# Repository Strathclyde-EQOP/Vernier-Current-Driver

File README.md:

# Vernier Current Driver

The Vernier Current Driver is an ultra low noise, programmable, bi-polar current source. It comes in two flavours:

1. Low Current Driver (LCD): designed to output current up to ~50 mA
2. High Current Driver (HCD): designed to output currents from ~50 mA to ~250 mA

## Releases

Checkout the [latest release](https://github.com/Strathclyde-EQOP/Vernier-Current-Driver/releases/latest) to download the latest verified version of the design. Releases include PDF schematics and gerber files, so there is no need to install/understand KiCAD in order to make a board.

Checkout the [dev branch](https://github.com/Strathclyde-EQOP/Vernier-Current-Driver/tree/dev) for the most up to date (but probably untested!) design.

## Performance

Three sample devices have been tested. For full details, see the companion paper or take a look a look in the [Testing](/Doc/Testing/) folder.

The headlines results:

|Configuration|CH1|CH2|CH3|
|---|---|---|---|
|LCD@10 mA<sub>MAX</sub> (10 ± 5 Hz average noise) | 151.1 pA√Hz | 147.4 pA√Hz | 146.3 pA√Hz |
|LCD@2.5 mA<sub>MAX</sub> (10 ± 5 Hz average noise) | 37.6 pA√Hz | 38.2 pA√Hz | 37.7 pA√Hz |
|HCD@250 mA<sub>MAX</sub> (10 ± 5 Hz average noise) | 4114.2 pA√Hz | 4125.3 pA√Hz | 4124.1 pA√Hz |
|LCD@10 mA<sub>MAX</sub> (10 ± 5 Hz relative average noise) | 15.05 ppb√Hz | 14.68 ppb√Hz | 14.57 ppb√Hz |
|LCD@2.5 mA<sub>MAX</sub> (10 ± 5 Hz relative average noise) | 15.06 ppb√Hz | 15.29 ppb√Hz | 15.10 ppb√Hz |
|HCD@250 mA<sub>MAX</sub> (10 ± 5 Hz relative average noise) | 16.46 ppb√Hz | 16.50 ppb√Hz | 16.50 ppb√Hz |

## Manual

For more information checkout the [Getting Started Guide](Doc/README.md).

## Publication

If you're the academic type, lots more detail on the design and testing of the Vernier Current Source can be found in our open-access paper, available as a pre-print on [arXiv](https://arxiv.org/abs/2207.10348).

## Citing

When citing this work in an academic context, please cite the paper as you normally would.

Outside of academic work, please link directly to this GitHub repo.

Lastly, if you make one and you like it (or don't like it), we would love to know!

## License

This work is licensed under a [Creative Commons Attribution-ShareAlike 4.0 International License](https://creativecommons.org/licenses/by-sa/4.0/).

## Authors

This work was created by [Marcin Mrozowski](https://eqop.phys.strath.ac.uk/people/marcin-mrozowski/) and [Iain Chalmers](https://www.linkedin.com/in/iain-chalmers-0394753b)
from the [Experimental Quantum Optics and Photonics](http://photonics.phys.strath.ac.uk/)
group at the University of Strathclyde.

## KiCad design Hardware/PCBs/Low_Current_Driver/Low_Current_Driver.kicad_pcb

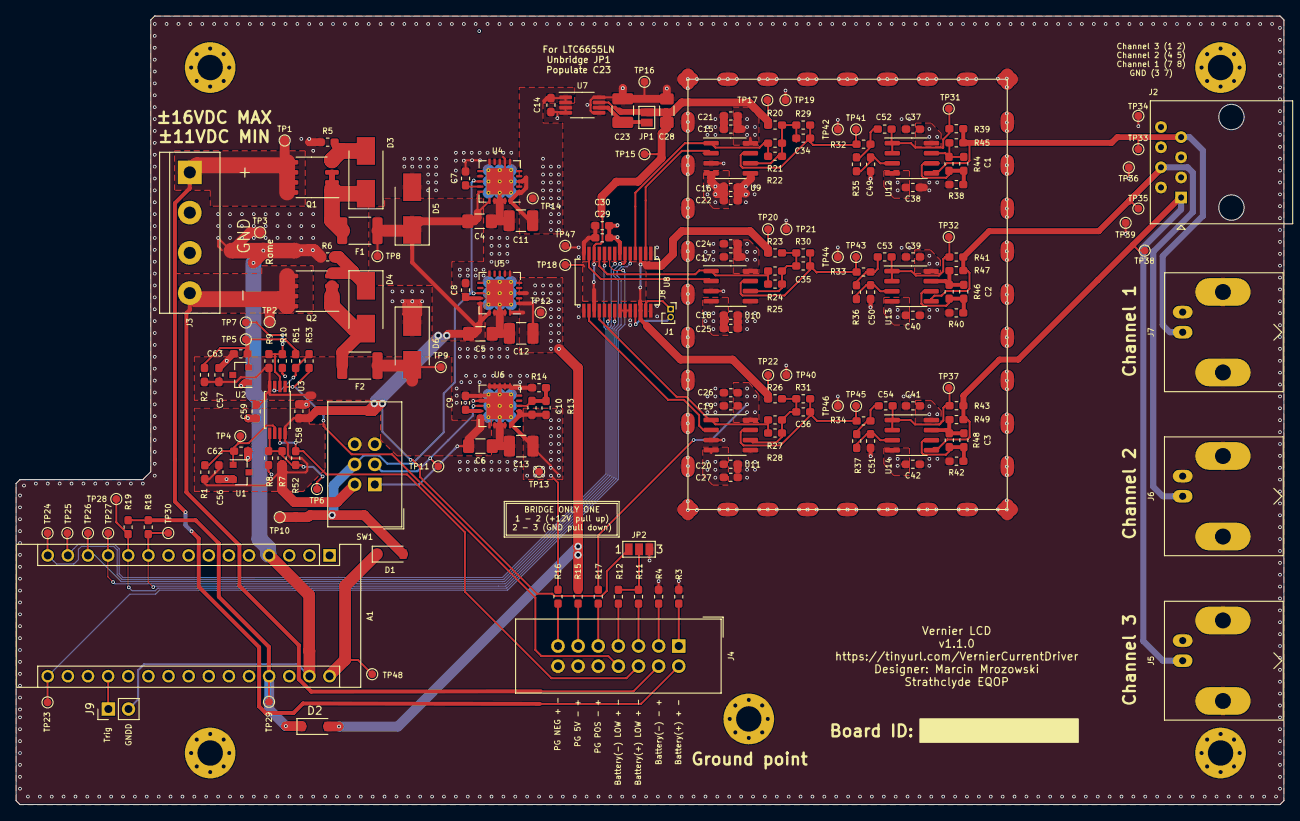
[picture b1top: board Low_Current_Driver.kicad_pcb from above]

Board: 4 copper layers, 160.0 x 99.5 mm, 194 parts (0 on the bottom side), 78 nets.

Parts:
A1: Arduino_Nano_Every; Arduino_Nano
C1, C2, C3, C7, C8, C9, C21, C22, C24, C25, C26, C27, C49, C50, C51, C52, C53, C54: 1u; C_0603_1608Metric_Pad1.05x0.95mm_HandSolder
C4, C5, C6, C28: 10u; C_1206_3216Metric_Pad1.42x1.75mm_HandSolder
C10, C29: 10n; C_0603_1608Metric_Pad1.05x0.95mm_HandSolder
C11, C12, C13, C23: 47u; C_1210_3225Metric_Pad1.42x2.65mm_HandSolder
C14, C15, C16, C17, C18, C19, C20, C30, C34, C35, C36, C37, C38, C39, C40, C41, C42, C56, C57, C58, C59, C62, C63: 100n; C_0603_1608Metric_Pad1.05x0.95mm_HandSolder
D1, D2: MBR0520LT; D_SOD-123
D3, D4, D5, D6: SMBJ16A; D_SMB_Handsoldering
F1, F2: 1A; Fuse_1812_4532Metric_Pad1.30x3.40mm_HandSolder
H1, H2, H3, H4, H5: MountingHole_Pad; MountingHole_3.2mm_M3_Pad_Via
J1: Conn_01x02; PinSocket_1x02_P1.00mm_Vertical_CUSTOM_CYD
J2: RJ45; RJ45_Amphenol_54602-x08_Horizontal
J3: Screw_Terminal_01x04; TerminalBlock_bornier-4_P5.08mm
J4: Conn_02x07_Odd_Even; IDC-Header_2x07_P2.54mm_Vertical
J5: Channel 3; BNC_Amphenol_B6252HB-NPP3G-50_Horizontal
J6: Channel 2; BNC_Amphenol_B6252HB-NPP3G-50_Horizontal
J7: Channel 1; BNC_Amphenol_B6252HB-NPP3G-50_Horizontal
J8: MS548-10F; MS548-10C
J9: Conn_01x02; PinHeader_1x02_P2.54mm_Vertical
JP1: SolderJumper_2_Open; SolderJumper-2_P1.3mm_Open_Pad1.0x1.5mm
JP2: SolderJumper_3_Open; SolderJumper-3_P1.3mm_Open_Pad1.0x1.5mm_NumberLabels
NT1: Net-Tie_3; NetTie-3_SMD_Pad2.0mm
Q1: Si4447ADY; SO-8_3.9x4.9mm_P1.27mm
Q2: IRF8707PbF; SO-8_3.9x4.9mm_P1.27mm
R1, R2, R3, R4, R5, R6, R11, R12, R15, R16, R17, R18, R19, R20, R21, R22, R23, R24, R25, R26, R27, R28, R29, R30, R31: 10k; R_0603_1608Metric_Pad1.05x0.95mm_HandSolder
R7: 120k; R_0603_1608Metric_Pad1.05x0.95mm_HandSolder
R8, R10: 100k; R_0603_1608Metric_Pad1.05x0.95mm_HandSolder
R9, R53: 133k; R_0603_1608Metric_Pad1.05x0.95mm_HandSolder
R13: 549k; R_0603_1608Metric_Pad1.05x0.95mm_HandSolder
R14: 102k; R_0603_1608Metric_Pad1.05x0.95mm_HandSolder
R32, R33, R34, R35, R36, R37, R38, R39, R40, R41, R42, R43, R44, R45, R46, R47, R48, R49: 1k; R_0603_1608Metric_Pad1.05x0.95mm_HandSolder
R51: 3k; R_0603_1608Metric_Pad1.05x0.95mm_HandSolder
R52: 2M; R_0603_1608Metric_Pad1.05x0.95mm_HandSolder
SW1: DPDT_Hirose; IDC-Header_2x03_P2.54mm_Vertical
TP1, TP2, TP3, TP4, TP5, TP6, TP7, TP8, TP9, TP10, TP11, TP12, TP13, TP14, TP15, TP16, TP17, TP18, TP19, TP20, TP21, TP22, TP23, TP24, TP25, TP26, TP27, TP28, TP29, TP30, TP31, TP32, TP33, TP34, TP35, TP36, TP37, TP38, TP39, TP40, TP41, TP42, TP43, TP44, TP45, TP46, TP47, TP48: TestPoint_Probe; TestPoint_Pad_D1.0mm
U1, U2: LM4040DBZ-5; SOT-23
U3: LM393; TSSOP-8_4.4x3mm_P0.65mm
U4, U5: TPS7A470x; QFN-20-1EP_5x5mm_P0.65mm_EP3.35x3.35mm_ThermalVias
U6: TPS7A33; QFN-20-1EP_5x5mm_P0.65mm_EP3.35x3.35mm_ThermalVias
U7: LTC6655-2.5; MSOP-8_3x3mm_P0.65mm
U8: DAC8814; SSOP-28_5.3x10.2mm_P0.65mm
U9, U10, U11, U12, U13, U14: OPA2210; SOIC-8_3.9x4.9mm_P1.27mm

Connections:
+5V: C12.1, C29.1, C30.1, D2.2, R15.1, TP12.1, U5.1, U5.3, U5.20, U8.7
+5VD: A1.27, D2.1, R18.2, R19.2, TP29.1
+7V5: C11.1, C14.1, C15.1, C17.1, C19.1, C21.1, C24.1, C26.1, C37.1, C39.1, C41.1, R17.1, TP14.1, U4.1, U4.3, U4.20, U7.1, U7.2, U9.8, U10.8, U11.8, U12.8, U13.8, U14.8
+12V_batt_post: D1.2, SW1.4, TP10.1, U4.13, U5.13
+BATT: J3.1, J4.2, Q1.5, Q1.6, Q1.7, Q1.8, TP1.1
-7V5: C10.1, C13.1, C16.2, C18.2, C20.2, C22.2, C25.2, C27.2, C38.2, C40.2, C42.2, R13.1, R16.1, TP13.1, U6.1, U6.2, U6.20, U9.4, U10.4, U11.4, U12.4, U13.4, U14.4
-BATT: J3.4, J4.4, Q2.5, Q2.6, Q2.7, Q2.8, TP2.1
/Channel_Outputs/4Q_DAC_OUT_1: C34.2, R29.2, R32.2, TP41.1, U9.7
/Channel_Outputs/4Q_DAC_OUT_2: C35.2, R30.2, R33.2, TP43.1, U10.7
/Channel_Outputs/4Q_DAC_OUT_3: C36.2, R31.2, R34.2, TP45.1, U11.7
/Channel_Outputs/Coil_Iout_1: J2.7, J7.1, R39.1, R45.2, TP33.1, U12.5
/Channel_Outputs/Coil_Iout_2: J2.4, J6.1, R41.1, R47.2, TP35.1, U13.5
/Channel_Outputs/Coil_Iout_3: J2.1, J5.1, R43.1, R49.2, TP38.1, U14.5
/DAC/CLK: A1.16, TP23.1, U8.9
/DAC/Iout_D: J1.1, U8.27
/DAC/MSB: A1.11, R19.1, TP28.1, U8.5
/DAC/Rrb_D: J1.2, U8.25
/DAC/SDI: A1.14, TP25.1, U8.10
/DAC/SDO: A1.15, TP24.1, U8.20
/DAC/Vref_2.5V: C28.1, JP1.2, R20.1, R23.1, R26.1, TP15.1, TP17.1, TP18.1, TP20.1, TP22.1, U7.7, U8.3, U8.12, U8.17, U8.26
/DAC/~CS: A1.13, TP26.1, U8.8
/DAC/~LDAC: A1.12, TP27.1, U8.21
/DAC/~RS: A1.10, R18.1, TP30.1, U8.6
/MCU/Trigger: A1.19, J9.1
/Power/+12VDC_bat: C4.1, C5.1, C56.1, C58.1, D5.1, F1.1, JP2.1, R1.2, R7.1, SW1.2, TP8.1, U3.8, U4.15, U4.16, U5.15, U5.16
/Power/-12VDC_bat: C6.1, C57.1, C59.1, D6.2, F2.1, R2.2, R9.1, SW1.1, TP9.1, U3.4, U6.15, U6.16
/Power/-EN: SW1.3, TP11.1, U6.13
/Power/Battery_Management/+5V_c_ref: C62.1, R1.1, TP4.1, U1.1, U3.6
/Power/Battery_Management/+5_PG_A: J4.11, R15.2
/Power/Battery_Management/+7.5_PG_A: J4.9, R17.2
/Power/Battery_Management/-5V_c_ref: C63.1, R2.1, R51.2, TP5.1, U2.2
/Power/Battery_Management/-7.5_PG_C: J4.13, R16.2
/Power/Battery_Management/Battery+_C: J4.1, R3.1
/Power/Battery_Management/Battery+_LOW_A: J4.5, R11.2
/Power/Battery_Management/Battery+_LOW_C: J4.6, R52.1, U3.7
/Power/Battery_Management/Battery-_A: J4.3, R4.1
/Power/Battery_Management/Battery-_LOW_A: J4.7, R12.2
/Power/Battery_Management/Battery-_LOW_C: J4.8, R53.1, U3.1
GND: C4.2, C5.2, C6.2, C7.2, C8.2, C9.2, C11.2, C12.2, C13.2, C14.2, C15.2, C16.1, C17.2, C18.1, C19.2, C20.1, C21.2, C22.1, C23.2, C24.2, C25.1, C26.2, C27.1, C28.2, C29.2, C30.2, C37.2, C38.1, C39.2, C40.1, C41.2, C42.1, C49.2, C50.2, C51.2, C56.2, C57.2, C58.2, C59.2, C62.2, C63.2, D5.2, D6.1, H1.1, H2.1, H3.1, H4.1, H5.1, J2.2, J2.3, J2.5, J2.6, J2.8, J3.2, J3.3, J4.10, J4.12, J4.14, J5.2, J6.2, J7.2, J8.1, JP2.3, NT1.1, NT1.3, R3.2, R4.2, R5.2, R6.2, R8.2, R10.2, R14.2, R38.2, R40.2, R42.2, SW1.5, SW1.6, TP3.1, TP16.1, TP19.1, TP21.1, TP34.1, TP36.1, TP39.1, TP40.1, TP42.1, TP44.1, TP46.1, TP47.1, U1.2, U2.1, U4.6, U4.7, U4.8, U4.9, U4.10, U4.12, U4.17, U4.18, U4.19, U4.21, U5.6, U5.7, U5.10, U5.17, U5.18, U5.19, U5.21, U6.6, U6.7, U6.8, U6.9, U6.10, U6.11, U6.12, U6.17, U6.18, U6.19, U6.21, U7.3, U7.4, U7.5, U7.8, U8.1, U8.14, U8.15, U8.22, U8.23, U8.24, U8.28, U9.3, U9.5, U10.3, U10.5, U11.3, U11.5
GNDD: A1.4, A1.29, J9.2, NT1.2
unnamed: A1.30, D1.1, TP48.1
unnamed: C1.1, R44.1, R45.1, U12.7
unnamed: C1.2, R38.1, R44.2, U12.6
unnamed: C2.1, R46.1, R47.1, U13.7
unnamed: C2.2, R40.1, R46.2, U13.6
unnamed: C3.1, R48.1, R49.1, U14.7
unnamed: C3.2, R42.1, R48.2, U14.6
unnamed: C7.1, U4.14
unnamed: C8.1, U5.14
unnamed: C9.1, U6.14
unnamed: C10.2, R13.2, R14.1, U6.3
unnamed: C23.1, JP1.1, U7.6
unnamed: C34.1, R20.2, R21.2, R22.2, R29.1, U9.6
unnamed: C35.1, R23.2, R24.2, R25.2, R30.1, U10.6
unnamed: C36.1, R26.2, R27.2, R28.2, R31.1, U11.6
unnamed: C49.1, R35.1, U12.3
unnamed: C50.1, R36.1, U13.3
unnamed: C51.1, R37.1, U14.3
unnamed: C52.1, R39.2, TP31.1, U12.1, U12.2
unnamed: C52.2, R32.1, R35.2
unnamed: C53.1, R41.2, TP32.1, U13.1, U13.2
unnamed: C53.2, R33.1, R36.2
unnamed: C54.1, R43.2, TP37.1, U14.1, U14.2
unnamed: C54.2, R34.1, R37.2
unnamed: D3.1, F1.2, Q1.1, Q1.2, Q1.3
unnamed: D3.2, Q1.4, R5.1
unnamed: D4.1, Q2.4, R6.1
unnamed: D4.2, F2.2, Q2.1, Q2.2, Q2.3
unnamed: JP2.2, R11.1, R12.1
unnamed: R9.2, R10.1, TP7.1, U3.2
unnamed: R21.1, R22.1, U8.4, U9.1
unnamed: R24.1, R25.1, U8.11, U10.1
unnamed: R27.1, R28.1, U8.18, U11.1
unnamed: R51.1, R53.2, U3.3
unnamed: R7.2, R8.1, R52.2, TP6.1, U3.5
unnamed: U8.2, U9.2
unnamed: U8.13, U10.2
unnamed: U8.16, U11.2

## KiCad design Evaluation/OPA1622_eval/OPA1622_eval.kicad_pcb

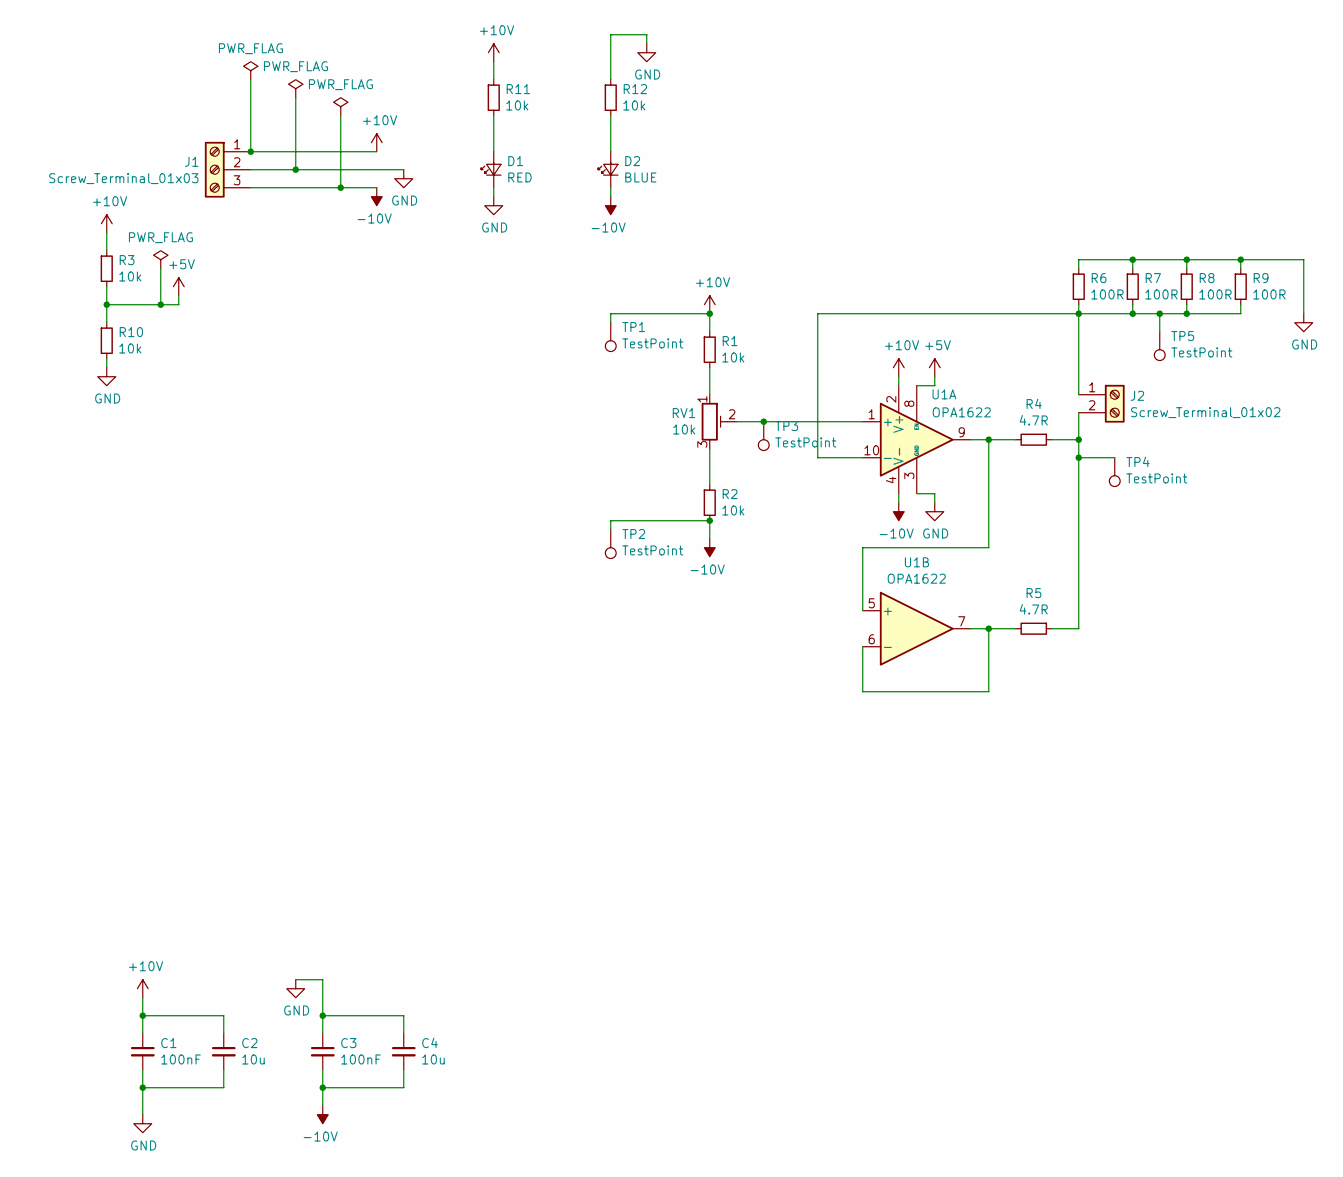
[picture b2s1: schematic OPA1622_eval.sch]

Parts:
C1, C3: 100nF; C_0805_2012Metric_Pad1.15x1.40mm_HandSolder
C2, C4: 10u; C_0805_2012Metric_Pad1.15x1.40mm_HandSolder
D1: RED; LED_0603_1608Metric_Pad1.05x0.95mm_HandSolder
D2: BLUE; LED_0603_1608Metric_Pad1.05x0.95mm_HandSolder
J1: Screw_Terminal_01x03; TerminalBlock_bornier-3_P5.08mm
J2: Screw_Terminal_01x02; TerminalBlock_bornier-2_P5.08mm
R1, R2, R3, R10, R11, R12: 10k; R_0805_2012Metric_Pad1.15x1.40mm_HandSolder
R4, R5: 4.7R; R_0805_2012Metric_Pad1.15x1.40mm_HandSolder
R6, R7, R8, R9: 100R; R_1206_3216Metric_Pad1.42x1.75mm_HandSolder
RV1: 10k; Potentiometer_Bourns_3296Y_Vertical
TP1, TP2, TP3, TP4, TP5: TestPoint; TestPoint_THTPad_1.0x1.0mm_Drill0.5mm
U1: OPA1622; Texas_S-PVSON-N10_ThermalVias

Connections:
+5V: R3.2, R10.1, U1.8 (EN)
+10V: C1.1, C2.1, J1.1, R1.1, R3.1, R11.1, TP1.1, U1.2 (V+)
-10V: C3.2, C4.2, D2.1 (K), J1.3, R2.2, TP2.1, U1.4 (V-), U1.11 (V-)
GND: C1.2, C2.2, C3.1, C4.1, D1.1 (K), J1.2, R6.1, R7.1, R8.1, R9.1, R10.2, R12.1, U1.3 (GND)
unnamed: D1.2 (A), R11.2
unnamed: D2.2 (A), R12.2
unnamed: J2.1, R6.2, R7.2, R8.2, R9.2, TP5.1, U1.10 (-)
unnamed: J2.2, R4.1, R5.1, TP4.1
unnamed: R1.2, RV1.1
unnamed: R2.1, RV1.3
unnamed: R4.2, U1.5 (+), U1.9
unnamed: R5.2, U1.6 (-), U1.7
unnamed: RV1.2, TP3.1, U1.1 (+)

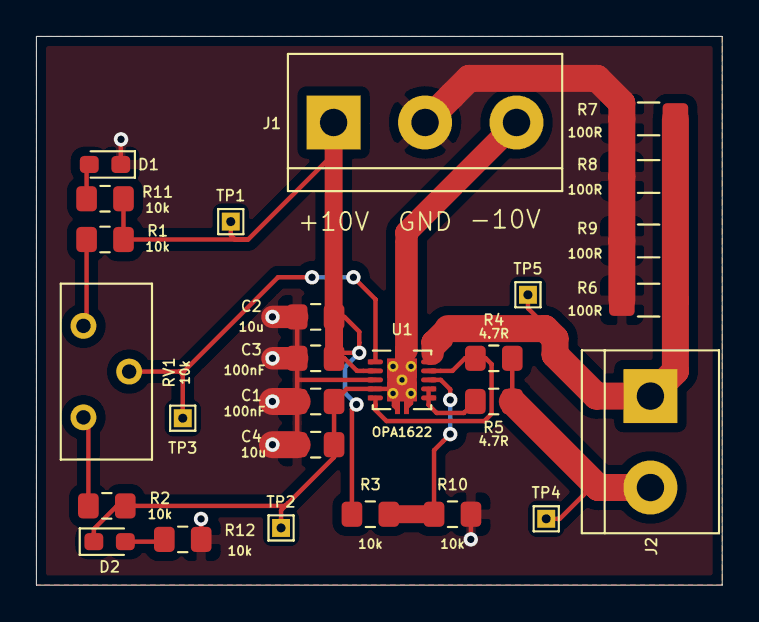
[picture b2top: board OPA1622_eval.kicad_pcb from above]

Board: 2 copper layers, 38.1 x 30.5 mm, 27 parts (0 on the bottom side), 13 nets.

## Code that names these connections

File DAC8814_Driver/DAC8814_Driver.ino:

#include <SPI.h>



#define SCLK 13
#define SDO 12
#define SDI 11
#define SS 10
#define LDAC 9
#define MSB 8

const byte numChars = 9;
char receivedChars[numChars];

int DAC_adress = 0;
long DAC_count = 0;

boolean newData = false;


void setup()
{
  pinMode(SS, OUTPUT);
  pinMode(LDAC, OUTPUT);
  
  Serial.begin(19200);
  SPI.begin();
  SPI.beginTransaction (SPISettings (2000000, MSBFIRST, SPI_MODE0));
  digitalWrite(SS,HIGH);
  digitalWrite(LDAC,HIGH);
  Serial.println("Enter DAC adress and Counts <1A500> Adress 0-2 Counts 0-65535");
  Serial.println();
}

//============

void loop() {
   
    recvWithStartEndMarkers();
    if (newData == true) 
    {
        parseData();
        setValue(DAC_adress, DAC_count);
        showParsedData();
        newData = false;
    }
}

// Start stop markers definition
void recvWithStartEndMarkers() 
{
    static boolean recvInProgress = false;
    static byte ndx = 0;
    char startMarker = '<';
    char endMarker = '>';
    char rc;

    while (Serial.available() > 0 && newData == false) 
    {
        rc = Serial.read();

        if (recvInProgress == true) 
        {
            if (rc != endMarker) 
            {
                receivedChars[ndx] = rc;
                ndx++;
                if (ndx >= numChars) 
                {
                    ndx = numChars - 1;
                }
            }
            else 
            {
                receivedChars[ndx] = '\0'; // terminate the string
                recvInProgress = false;
                ndx = 0;
                newData = true;
            }
        }

        else if (rc == startMarker) 
        {
            recvInProgress = true;
        }
    }
}

void setValue(int DAC_adress, long DAC_count)
{
  digitalWrite(SS, LOW);
  SPI.transfer(DAC_adress);           // Adress followed by counts
  SPI.transfer(highByte(DAC_count)); 
  SPI.transfer(lowByte(DAC_count)); 
  digitalWrite(SS, HIGH);
  digitalWrite(LDAC, LOW);            //LDAC for synchornisation
  delayMicroseconds(1);               //
  digitalWrite(LDAC, HIGH);           //
 
}


// Split the data into its parts
void parseData() 
{      

    char * strtokIndx;                            // This is used by strtok() as an index

   
    strtokIndx = strtok(receivedChars, "A");      // Start with adress
    DAC_adress = atoi(strtokIndx);                // Convert this part to an integer
    
    if (DAC_adress > 2) DAC_adress = 2;           // Limit DAC to 3 channels only
    if (DAC_adress < 0) DAC_adress = 0;           //
    

    strtokIndx = strtok(NULL, "A");
    DAC_count = atol(strtokIndx);                 // Convert this part to a long integer
    if (DAC_count > 65535) DAC_count = 65535;
    if (DAC_count < 0) DAC_count = 0;
    

}

// Repeat how DAC was setup through UART
void showParsedData() 
{
    Serial.print("DAC ");
    Serial.print(DAC_adress);
    Serial.print("Count ");
    Serial.print(DAC_count);
    Serial.println();
}

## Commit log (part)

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2020-03-13 Add files via upload
    Changed standard 2.54 mm connectors to Hirose DF11 series which are keyed.
    Revised some copper islands and optimised connections and labeling
    Added an interactive BOM to help with assembly
2020-03-16 2 mA coil driver WiP
    Update on work in progress 2 mA coil driver
2020-03-31 DAC8814 driver
    Added DAC8814 driver
2020-04-02 Update PDFs
    update PDFs to match schematics
2020-04-30 Deleted bak files and pdfs
2020-04-30 Update .gitignore
    Added html BOMS to the list.
2020-04-30 Removed interactive BOMs
    These will be present in the tagged release.
2020-05-04 OPA1622 Power Pad Tented Vias
    -Created a footprint for OPA1622 that features tented vias on the power pad
    -Applied it to the schematic as well as layout
2020-05-12 200mA changes
    -Changed OPA1622 footprint to accommodate tented vias
    -Rounded edges of the board to reduce mechanical stress
    -Refined drawing dimensions
    -Added title block to every schematic and layout sheet.
2020-05-12 Applied 1.0B changes to 2mA version
2020-05-18 Cleaned redundant project files
    KiCad automatically creates project file when individual schematic sheet is opened.
2020-07-13 HCP output fix
    Fixed the HCP output.
2020-07-13 SPI fix
    Rewired the SDI and SDO so that they match the host pinout.
2020-11-06 1.0C Initial commit
    -Fixed amplifier output
    -Changed connectors to IDC
    -Via perimeter added
    TODO:
    Add shielding over analogue section
2020-11-11 Issue fixes
    This commit, addresses following issues:
    -Stray current at the output with only USB plugged in
    -RFI Shield over analogue circuitry
    -Wrong BNC connector footprint
    Some general layout optimisation
2020-11-12 Silkscreen fixes
    Silkscreen settings changed so that references are not obstructed by the shield.
    -Added magnetic field direction designation for each channel.
2021-04-21 Update README.md
    Initial version.
    TODO;
    - Add picture of the coil driver
    - Expand on the intro
2021-05-18 1.0D Update
    LCCD changes
    -Addition of trigger for calibration
    -PCB optimisation
    HCCD changes
    -New output stage designed
    -Changes from 1.0C applied to HCCD
2021-05-19 Silkscreen cleanup
    -Silkscreen cleanup
    -Unconnected items removed
    -Addition of calibration software
    -Addition of test points for shunt resistor on the bottom layer
2022-03-24 Create CITATION.cff
    Added citation.cff to the project.
2022-03-29 Fix line endings
2022-03-29 Add BAUDRATE as config option
2022-03-29 Remove dead commented out code
2022-03-29 Add CoilDriver class files
2022-03-29 Define CoilDriver class
2022-03-29 Remove unused pin definitions
2022-03-29 Implement CoilDriver::begin method
2022-03-29 Implement CoilDriver::set_dac method
2022-03-29 Increase serial baudrate
    No need for it to be so low.
2022-03-29 Add set_all_dac method
2022-03-29 Store DAC setpoint on set
2022-03-29 Replace calibration routine
    Previously, the array-per-channel meant needing to switch on the channel. Just making this a 2D array makes the code much cleaner.
2022-03-29 Remove unused calibration correction
    Existing code wasn't even using the calibration routine...
2022-03-30 Refactor numChars global to kSerialRxBufferLength
    Starting to move towards the Google C++ style guide.
2022-03-30 Replace #defines with consts
2022-03-30 Reduce scope of kNumChannels
2022-03-30 Fix stored setpoint
    Originally was storing the calibrated code sent to the DAC, but calibration should be transparent to the user. As such, store the code the user requested.
2022-03-30 Formatting cleanup
2022-03-30 Refactor recvWithStartEndMarkers
    Removed the need for the newData global. Renamed to better reflect functionality.
2022-03-30 Increase rx serial buffer size
    New commands will potentially be much longer than the old maximum of 9 characters.
2022-03-30 Drop overflowing rx buffers
    Previosuly, the parser would just keep replacing the last character in the buffer (which would then get overwritten with \0 anyway). Any command that overflows the buffer is by definition invalid. Th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
2022-03-30 Refactor variable names
    Match google style guide, and make more descriptive.
2022-03-30 Add return value on SetChannel methods
2022-03-30 Change valid channel range to be 0-index based
    Although the intention is to move to 1-based indexing to match the channel names on the PCB, this needs tweaked in a number of places in the code. For now, stick with 0-based indexing.
2022-03-30 Remove redundant validity check
2022-03-30 Move all legacy functionality into ProcessLegacyCommand
2022-03-30 Remove unused include
2022-03-30 Remove superfluous comments
2022-03-31 Add '!chan' command
    Used to set a channel to a given setpoint.
    Format is '<{chan_number} {setpoint}>'.
2022-03-31 Fix ValidateChannels
    Accidentally had lower limits for 0-based index, and upper limit for 1-based index.
2022-03-31 Add '!ramp' command
    Currently just a placeholder with response. Not functional.
2022-03-31 Move setpoint storage to Channel instance
2022-03-31 Update ValidateChannel to match Channel addresses
2022-03-31 Refactor GetChannel to GetChannelSetpoint
2022-03-31 Add GetChannel method
2022-03-31 Refactor ValidateChannel
    Remove code duplication
2022-03-31 Refactor GetChannelSetpoint to use Channel objects
2022-03-31 Move channel addresses to be 1-based indexed
    This means that channel addresses now match the channel labels on the PCB/case.
    Legacy commands are maintained as 0-based indexing.
2022-03-31 Cleanup reset procedure
    The reset point is now not just a magic number, and could conceivably be conceivably be customised per channel.
2022-03-31 Set channel state to STATIC on SetChannelSetpoint
2022-03-31 Implement Begin
2022-03-31 Add Next implementation on Ramp
2022-03-31 Add InitRamp method on CoilDriver
2022-04-04 Rename Arduino sketch
2022-04-04 Refactor CoilDriver to CurrentSource
    More accurately reflects the general nature of the current source.
2022-04-04 Add section headings
2022-04-04 Fix calibration tables
    The old 2D correction table assumed channel number matched calibration table array index.
    Instead, store a pointer to the cirrection table for each channel so that the channel number is independent.
2022-04-04 Add input trigger capability
2022-04-04 Remove debug output
2022-04-04 Move software_version to end of struct
    Software version will not be stored in EEPROM. Moving it to the end of the struct will allow offsets from the EEPROM base address to mirror struct member offsets, without wasting space in the EEPROM.
2022-04-04 Add basic definitions for BoardInfo methods
2022-04-04 Rename BoardInfo to HardwareInfo
    The information stored in the EEPROM will be hardware-specific.
2022-04-04 Implement get/set MaxCurrent
2022-04-04 Add set/get max current commands
2022-04-05 Fix mistaken caps in method name
2022-04-05 Refactor out common code to new methods
2022-04-05 Move private methods to end of file
2022-04-05 Implement GetBoardId
2022-04-05 Refactor to use GetMaxCurrentEeprom
2022-04-05 Add EepromReadString helper method
2022-04-05 Add boardid commands
2022-04-05 Implement get/set for hardware_version
2022-04-05 Bump software version to 1.0.2
2022-04-05 Move Arduino firmware into Software folder
2022-04-05 Remove old DAC8814_Driver
2022-04-05 Move command registration to dedicated function
    Also minor whitepsace cleanup.
2022-04-05 Add descriptive headers to command callbacks
2022-04-05 Rename coil to current_source
    In EQOP we tend to use the current source as a coil driver, but that's not always the case!
2022-04-05 Add descriptive header to ProcessLegacyCommand
2022-05-04 Delete PSU/10mA directory
    Deleted no longer needed files
2022-05-04 Delete Datasheets directory
    Deleted no longer needed files
2022-05-04 Noise_analysis removal of old files
    Removal of unneeded files
2022-05-04 Change of name to Low Current Driver (LCD) folder
2022-05-04 Change of name to High Current Driver (HCD) folder
2022-05-05 Silkscreen update HCD
    Removed EQOP specific "X" "Y" "Z" from the channels
2022-05-05 Silkscreen update LCD
    Removed EQOP specific "X" "Y" "Z" from the channels
2022-05-05 LCD unused library removal
    Removed legacy symbols and old libraries
2022-05-05 HCD stale library removal
    Removed stale libraries
2022-05-13 Inital test analysis scripts
2022-05-18 Script cleanup
2022-05-18 Add calibration test data
2022-05-18 Rename for consistency
2022-05-18 Move noise tests to common folder
2022-05-18 Move noise analysis to common script
2022-05-18 Refactor to use get_spectrum helper
2022-05-19 Simplify plotting
2022-05-19 Update dataset name
2022-05-19 Fix scaling to ppm
2022-05-19 Simplify plot colours
2022-05-19 Add multi-channel support
2022-05-19 Generate analysis table in latex format
    Note that the data for the LCD configured for 2.5 mA need added.
2022-05-25 Use common frequency output of get_spectrum
    The datasets all end up with the same frequency axis so no need to track multiple copies of the same thing.
2022-05-25 Fix caps to for consistency
2022-05-25 Remove comment on data availability
    The stability data is small enough to just include in Git.
2022-05-25 Add noise_data.mat to .gitignore
    This is a > 70 MB file so definitely don't want it accidentally getting added to the repo!
2022-05-25 Add generation of combined plot for inclusion in README
2022-05-25 Update README with test results from paper
2022-05-25 Add noise spectra plot to README
2022-05-26 Remove placeholder citation
    People can just use the citation for the published paper directly.
2022-06-01 LCD amplifier update
    -Updated OPA2277 originally on the schematic to what was actually used on the board (OPA2210)
    -Added a DNP on one of the power mux diodes
2022-06-01 Add doc for how to customise drivers
2022-06-01 Add doc on HCD drive stage biasing
2022-06-01 Remove depreciated legacy command handling
    (cherry picked from commit e2e803c343cd77e2be174581dea688db01fe43f0)
2022-06-01 Refactor 'source' to 'driver'
    Standardised on 'Current Driver' as our terminology, rather than 'Current Source'
    (cherry picked from commit 016921325ebac01311636b537ec159552d6cfdce)
2022-06-01 Minor doc fixes
    (cherry picked from commit 1a61a697f7c94987b8b4524a1cd3ccbd30b58013)
2022-06-01 Add error code return on !next command
    (cherry picked from commit 33a847426ccdf50e6430a0daceca5ee3fd89d618)
2022-06-01 Add clarification in title
2022-06-01 Add reference to getting conencted
2022-06-06 LCD amplifier update
    -Updated OPA2277 amplifiers to OPA2210 that were actually populated on the boards
    -Added DNP to one of the power mux diodes
    -Updated nano symbol, so that it is taken from the library and not rescue
2022-06-06 HCD missing power flag on MCU fix
    Added the missing power flag that was on the diode power mux
2022-06-06 Add OPA2210 symbol
2022-06-06 LCD amplifier update
    - Updated OPA2277 amplifiers to OPA2210 that were actually populated on the boards.
2022-06-06 Fill zones on LCD PCB
2022-06-06 Update PCB from schematic
    There were no functional changes made. The netlist names were just slightly mismatched between the schematic and the PCB. Most the the difference from this commit are just line orderings seem to have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
2022-06-07 Add faceplate drawings
2022-06-07 Update .gitignore
    Remove KiCAD specific entries, as those are now specifed in the Hardware subdirectory.
    Add exclusion for VSCode history directories at any level.
2022-06-07 Add Releases section to README
2022-06-07 Fix symbol cache name
2022-06-07 Fix broken courtyard
2022-06-07 Add missing footprint
2022-06-07 Add missing file extension
2022-06-07 Fix library name for consistency
2022-06-07 Add missing OPA2210 symbol
2022-06-07 Remove old symbol libraries
2022-06-07 Replace OPA2270 with OPA2210
    These parts must have been missed somehow in 2617594b43217be702f357aa0c3cac4a60710900 and f9a9295af51ef93e9ca1b36aeebbcecdbb861685
2022-06-07 Place grid and drill/place origin at common location
    Just bottom left corner of the PCB.
2022-06-07 Fix malformed courtyard
2022-06-07 Bump version to 1.1.0
2022-06-08 Add license
2022-07-14 Fix caps in unit
2022-07-14 Update performance numbers and figure
